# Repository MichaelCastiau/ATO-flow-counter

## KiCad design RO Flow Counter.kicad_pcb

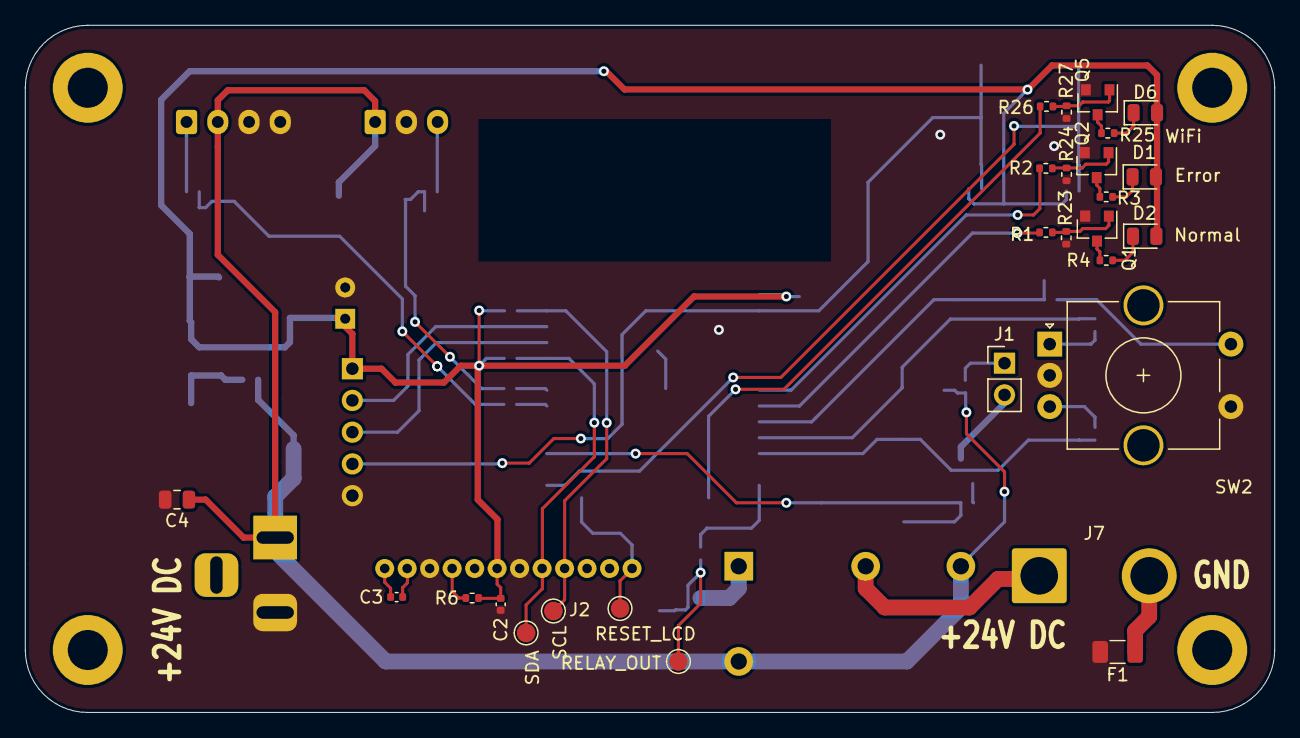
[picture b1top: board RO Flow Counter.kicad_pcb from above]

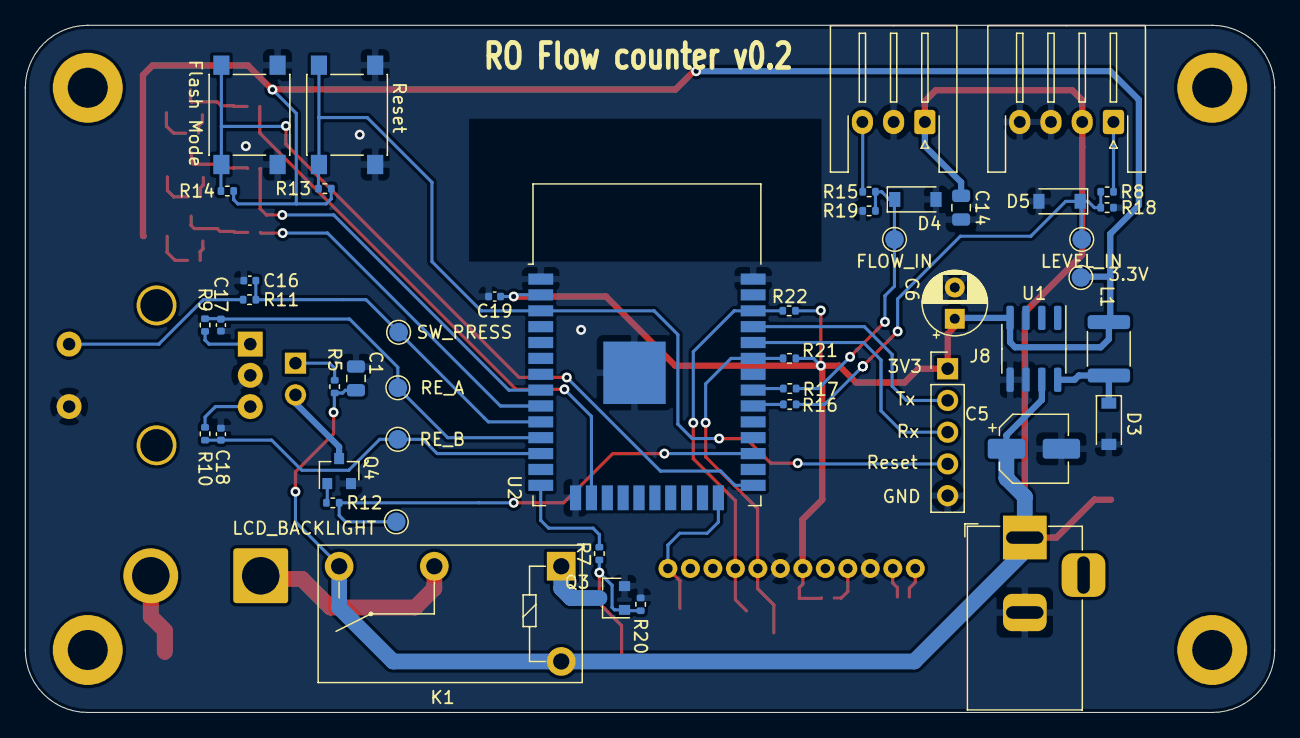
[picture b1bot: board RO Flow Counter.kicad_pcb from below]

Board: 2 copper layers, 100.0 x 55.0 mm, 79 parts (47 on the bottom side), 47 nets.

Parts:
C1, C4: 22uF; C_0805_2012Metric
C2, C3, C16: 100nF; C_0402_1005Metric
C5: 68uF; CP_Elec_5x5.4
C6: 120uF; CP_Radial_D5.0mm_P2.50mm
C14: 4.7uF; C_0805_2012Metric
C17, C18, C19: 0.1uF; C_0402_1005Metric
D1: Error; LED_0805_2012Metric
D2: Normal Operation; LED_0805_2012Metric
D3: 1N5817; D_SOD-123
D4, D5: 3V3; D_SOD-123
D6: WiFi; LED_0805_2012Metric
F1: 10A; Fuse_1206_3216Metric
H1, H2, H3, H4: MountingHole; MountingHole_3.2mm_M3_DIN965_Pad
J1: LCD Power; PinHeader_1x02_P2.54mm_Vertical
J2: Conn_01x12; ERC1602
J3: Barrel_Jack; BarrelJack_Horizontal
J5: Flow Meter; JST_XH_S3B-XH-A-1_1x03_P2.50mm_Horizontal
J6: Level Sensor (optional); JST_XH_S4B-XH-A-1_1x04_P2.50mm_Horizontal
J7: Conn_01x02; SolderWire-2.5sqmm_1x02_P8.8mm_D2.4mm_OD4.4mm
J8: Programming; PinHeader_1x05_P2.54mm_Vertical
K1: G5Q-1A; Relay_SPST_Omron-G5Q-1A
L1: 100uH; L_1812_4532Metric
Q1, Q2, Q3, Q4, Q5: 2N7002E; SOT-23
R1, R2, R7, R9, R10, R11, R12, R16, R17, R26: 1k; R_0402_1005Metric
R3: 154; R_0402_1005Metric
R4: 140; R_0402_1005Metric
R5: 1k4; R_0402_1005Metric
R6, R8, R13, R14, R19, R20, R23, R24, R27: 10k; R_0402_1005Metric
R15, R21, R22: 5k6; R_0402_1005Metric
R18: 1k56; R_0402_1005Metric
R25: 10; R_0402_1005Metric
SW2: Rotary_Encoder_Switch; RotaryEncoder_Alps_EC11E-Switch_Vertical_H20mm_CircularMoun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
SW3: Reset; SW_Push_1P1T_NO_6x6mm_H9.5mm
SW4: Flash Mode; SW_Push_1P1T_NO_6x6mm_H9.5mm
TP1: 3.3V; TestPoint_Pad_D1.5mm
TP2: SW_PRESS; TestPoint_Pad_D1.5mm
TP3: RE_A; TestPoint_Pad_D1.5mm
TP4: RELAY_OUT; TestPoint_Pad_D1.5mm
TP5: RE_B; TestPoint_Pad_D1.5mm
TP6: SDA; TestPoint_Pad_D1.5mm
TP7: LEVEL_IN; TestPoint_Pad_D1.5mm
TP8: RESET_LCD; TestPoint_Pad_D1.5mm
TP9: FLOW_IN; TestPoint_Pad_D1.5mm
TP11: SCL; TestPoint_Pad_D1.5mm
TP12: LCD_BACKLIGHT; TestPoint_Pad_D1.5mm
U1: LM2594HVM-3.3; SOIC-8_3.9x4.9mm_P1.27mm
U2: ESP32-WROOM-32

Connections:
+3V3: C2.1, C6.1, C19.1, D1.2, D2.2, D6.2, J2.7, J8.1, L1.2, R6.2, R13.1, R14.1, R21.1, R22.1, TP1.1, U1.4, U2.2
+24V: C1.2, C4.1, C5.1, C14.1, J3.1, J5.1, J6.2, K1.3, K1.5, R5.2, U1.7
/display/BACKLIGHT_LCD: R12.2, TP12.1, U2.27
/display/RESET_DISPLAY: J2.1, TP8.1, U2.24
/display/SCL: J2.4, R22.2, TP11.1, U2.36
/display/SDA: J2.5, R21.2, TP6.1, U2.33
/mcu/ERROR_OUT: R2.1, U2.8
/mcu/FLOW_IN: R17.1, U2.31
/mcu/LED_WIFI: R26.1, U2.16
/mcu/LEVEL_IN: R16.1, U2.30
/mcu/NORMAL_OPERATION_OUT: R1.1, U2.9
/mcu/RELAY_OUT: R7.2, U2.14
/mcu/RE_A: C17.1, R9.2, TP3.1, U2.11
/mcu/RE_B: C18.1, R10.2, TP5.1, U2.12
/mcu/RX: J8.3, U2.34
/mcu/SW_PRESS: C16.1, R11.1, TP2.1, U2.10
/mcu/TX: J8.2, U2.35
/mcu/reset: J8.4, R13.2, SW3.2, U2.3
GND: C1.1, C2.2, C4.2, C5.2, C6.2, C14.2, C16.2, C17.2, C18.2, C19.2, D3.2, D4.2, D5.2, F1.2, J2.6, J2.10, J3.2, J5.2, J6.3, J6.4, J8.5, Q1.2, Q2.2, Q3.2, Q4.2, Q5.2, R18.2, R19.2, R20.1, R23.1, R24.1, R27.1, SW2.C, SW2.S1, SW3.1, SW4.2, U1.5, U1.6, U2.1, U2.15, U2.38, U2.39
unnamed: C3.1, J2.12
unnamed: C3.2, J2.11
unnamed: D1.1, R3.1
unnamed: D2.1, R4.1
unnamed: D3.1, L1.1, U1.8
unnamed: D4.1, R15.2, R17.2, R19.1, TP9.1
unnamed: D5.1, R8.2, R16.2, R18.1, TP7.1
unnamed: D6.1, R25.1
unnamed: F1.1, J7.2
unnamed: J1.1, R5.1
unnamed: J1.2, Q4.3
unnamed: J2.9, R6.1
unnamed: J5.3, R15.1
unnamed: J6.1, R8.1
unnamed: J7.1, K1.2
unnamed: K1.1, Q3.3
unnamed: Q1.1, R1.2, R23.2
unnamed: Q1.3, R4.2
unnamed: Q2.1, R2.2, R24.2
unnamed: Q2.3, R3.2
unnamed: Q3.1, R7.1, R20.2, TP4.1
unnamed: Q4.1, R12.1
unnamed: Q5.1, R26.2, R27.2
unnamed: Q5.3, R25.2
unnamed: R9.1, SW2.A
unnamed: R10.1, SW2.B
unnamed: R11.2, SW2.S2
unnamed: R14.2, SW4.1, U2.25

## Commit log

2022-07-28 change to esp32
2022-08-16 fix rotary encoder, i2c pullup resistors, reset button placement
2022-08-16 fix tracing, lcd pads
2022-08-16 fix voltage level on flow sensor
2022-08-21 use mosfet for led instead of bjt
2022-08-23 finish v2
2022-08-23 fix ro GND pad
2022-08-23 fix lcd pads
2022-08-23 add archive
